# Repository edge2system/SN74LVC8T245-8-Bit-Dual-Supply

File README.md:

# SN74LVC8T245-8-Bit-Dual-Supply
two FPGA connection board
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

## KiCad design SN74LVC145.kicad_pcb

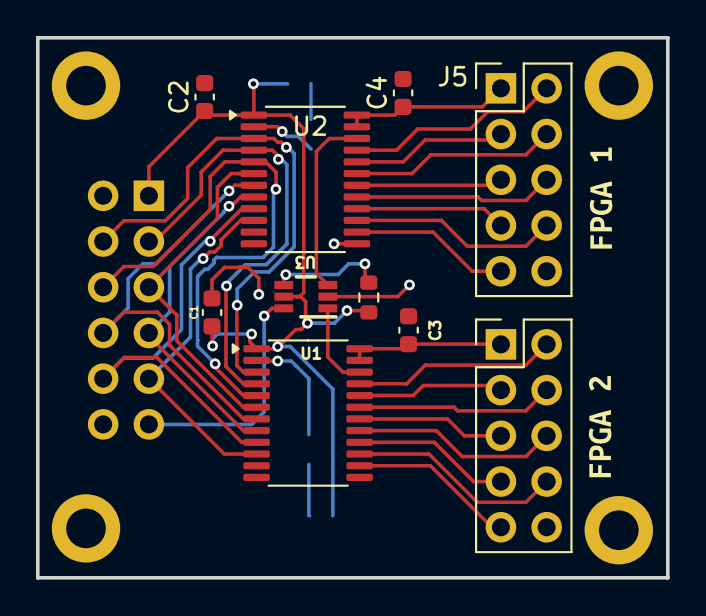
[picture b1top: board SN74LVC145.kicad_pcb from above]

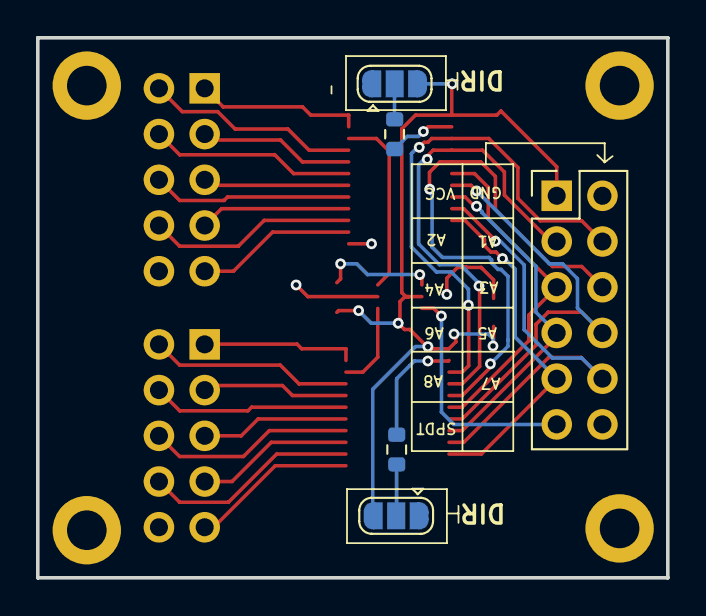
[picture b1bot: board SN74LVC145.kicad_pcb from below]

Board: 2 copper layers, 35.0 x 30.0 mm, 17 parts (5 on the bottom side), 36 nets.

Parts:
C1, C2, C3, C4: 0.1nf; C_0603_1608Metric
J1: Conn_02x06_Odd_Even; PinHeader_2x06_P2.54mm_Vertical
J4, J5: Conn_02x05_Odd_Even; PinHeader_2x05_P2.54mm_Vertical
JP1, JP2: SolderJumper_3_Open; SolderJumper-3_P1.3mm_Open_RoundedPad1.0x1.5mm
R1, R3: 25R; R_0603_1608Metric
R2: 25 R; R_0603_1608Metric
U1, U2: SN74LVC8T245; TSSOP-24_4.4x7.8mm_P0.65mm
U3: SN74LVC1G3157DCKR; DCK0006A_M
kibuzzard-67F7AC31: G***; kibuzzard-67F7AC31
kibuzzard-67F7AC44: G***; kibuzzard-67F7AC44

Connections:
/A1: J1.4, U1.3 (A1), U2.3 (A1)
/A2: J1.3, U1.4 (A2), U2.4 (A2)
/A3: J1.6, U1.5 (A3), U2.5 (A3)
/A4: J1.5, U1.6 (A4), U2.6 (A4)
/A5: J1.8, U1.7 (A5), U2.7 (A5)
/A6: J1.7, U1.8 (A6), U2.8 (A6)
/A7: J1.10, U1.9 (A7), U2.9 (A7)
/A8: J1.9, U1.10 (A8), U2.10 (A8)
/B1: J5.2, U2.21 (B1)
/B2: J5.3, U2.20 (B2)
/B3: J5.4, U2.19 (B3)
/B4: J5.5, U2.18 (B4)
/B5: J5.6, U2.17 (B5)
/B6: J5.7, U2.16 (B6)
/B7: J5.8, U2.15 (B7)
/B8: J5.9, U2.14 (B8)
/BB1: J4.2, U1.21 (B1)
/BB2: J4.3, U1.20 (B2)
/BB3: J4.4, U1.19 (B3)
/BB4: J4.5, U1.18 (B4)
/BB5: J4.6, U1.17 (B5)
/BB6: J4.7, U1.16 (B6)
/BB7: J4.8, U1.15 (B7)
/BB8: J4.9, U1.14 (B8)
/C_Signle: J1.11, U3.6 (S)
/OE: U2.22 (~OE), U3.3 (B1)
/OE_2: U1.22 (~OE), U3.1 (B2)
/VccA: C1.1, C2.1, J1.1, JP1.3 (B), JP2.3 (B), R2.2, U1.1 (V_{CCA}), U2.1 (V_{CCA}), U3.5 (VCC)
GND: C1.2, C2.2, C3.2, C4.2, J1.2, J4.10, J5.10, JP1.1 (A), JP2.1 (A), U1.11 (GND), U1.12 (GND), U1.13 (GND), U2.11 (GND), U2.12 (GND), U2.13 (GND), U3.2 (GND)
unnamed: C3.1, J4.1, U1.23 (V_{CCB}), U1.24 (V_{CCB})
unnamed: C4.1, J5.1, U2.23 (V_{CCB}), U2.24 (V_{CCB})
unnamed: JP1.2 (C), R1.1
unnamed: JP2.2 (C), R3.1
unnamed: R3.2, U1.2 (DIR)
unnamed: R1.2, U2.2 (DIR)
unnamed: R2.1, U3.4 (A)

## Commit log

2025-05-21 remove spdt switch
